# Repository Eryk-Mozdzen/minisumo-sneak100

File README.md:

# Autonomous minisumo robot Sneak100 

### DEADLINE:
```diff
#  4 sep 2021 - Baltic Robot Battles, Gdansk, Poland (canceled)
- 20 nov 2021 - EastROBO 2021, Bialystok, Poland (missed)
- 28 nov 2021 - ROBOmotion 2021, Rzeszow, Poland (missed)
+  9 apr 2022 - Robotic Tournament, Rybnik, Poland
# 13 may 2022 - Baltic Robot Battles, Gdansk, Poland (canceled)
+ 18 jun 2022 - XIII Robotic Arena, Wroclaw, Poland
-  2 jul 2022 - Drones And Robots Tournament, Krakow, Poland (missed)
+  4 nov 2022 - Robochallnge 2022, Bucharest, Romania
+ 26 nov 2022 - ROBOmotion 2022, Rzeszow, Poland
+  1 apr 2023 - Robotic Tournament, Rybnik, Poland
- 22 apr 2023 - XIV Robotic Arena, Wroclaw, Poland (malfunction)
- 14 may 2023 - Tournoi National de Robotique, Niem, France (malfunction)
```

### Next version:     
- develop spring for blade
- proximity sensors: turn to more front
- hide power switch

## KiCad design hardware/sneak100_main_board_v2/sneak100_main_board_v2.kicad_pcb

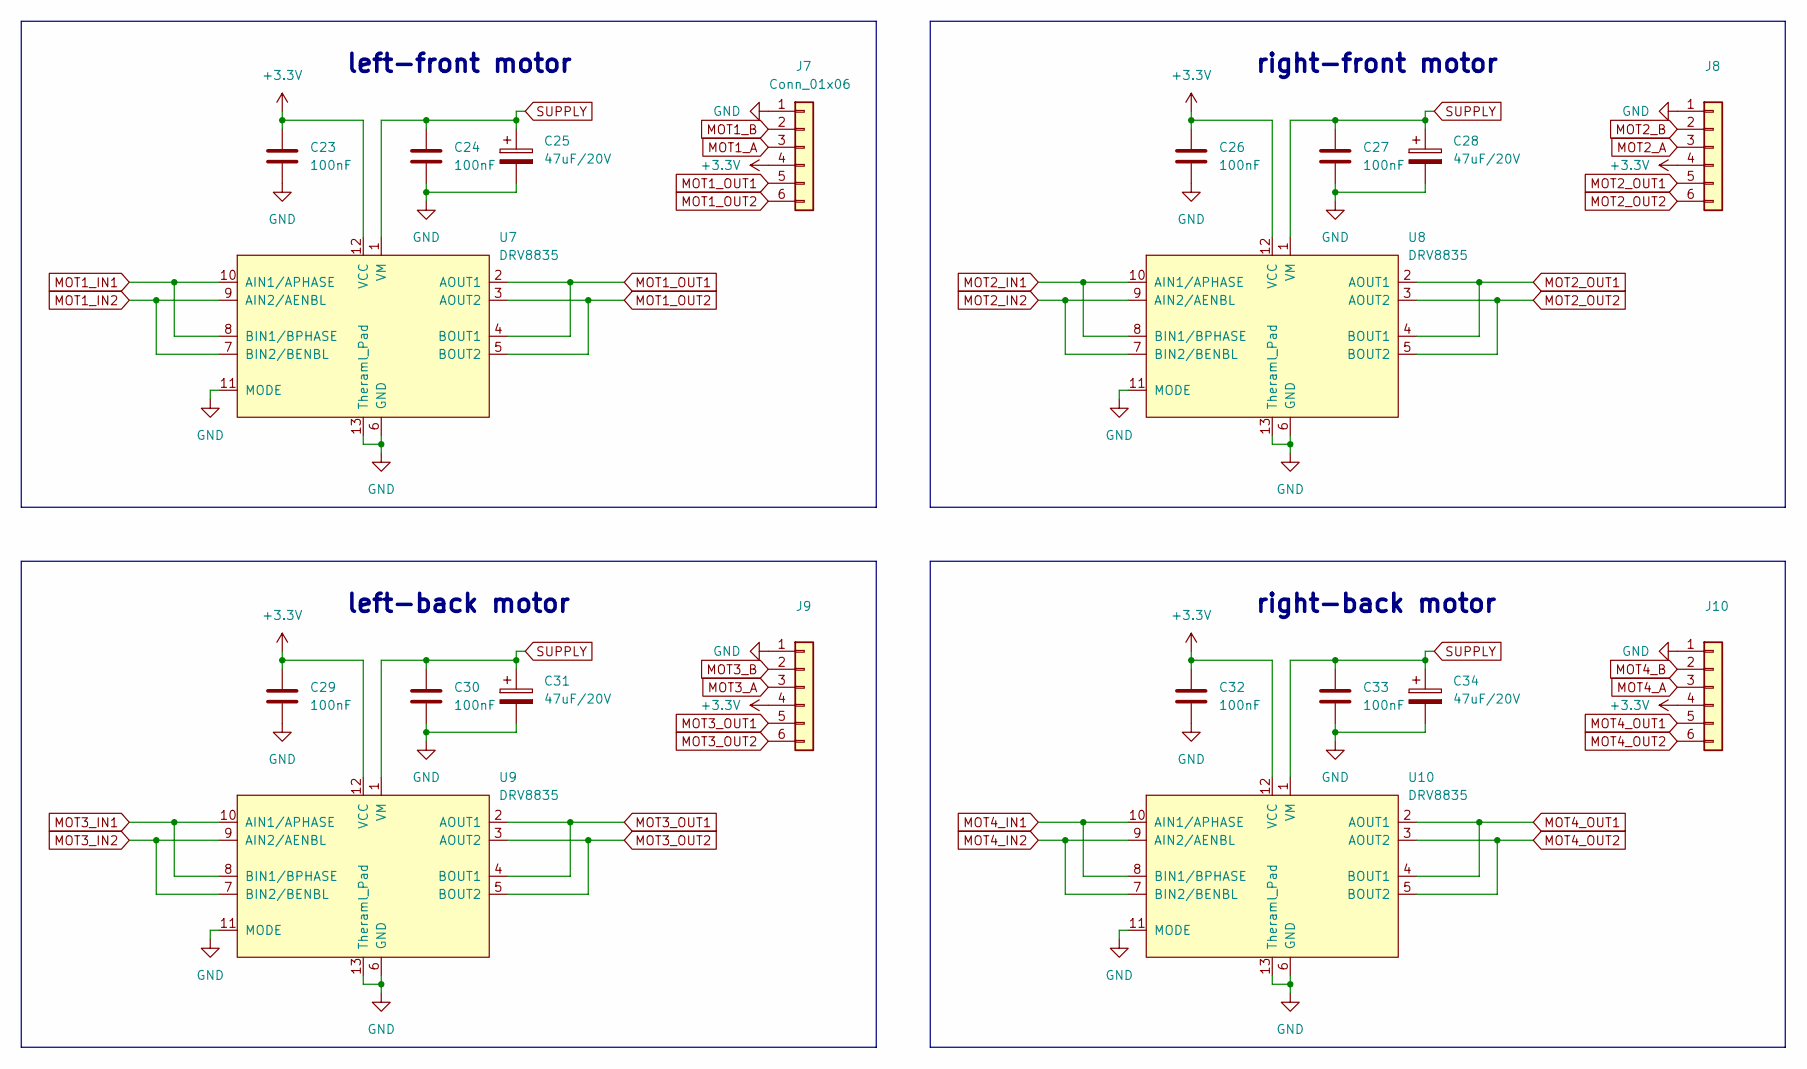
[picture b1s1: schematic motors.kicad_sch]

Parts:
C23, C24, C26, C27, C29, C30, C32, C33: 100nF
C25, C28, C31, C34: 47uF/20V
J7: Conn_01x06
J8, J9, J10: (no value)
U7, U8, U9, U10: DRV8835

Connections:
GND: C23.2, C24.2, C25.2, C26.2, C27.2, C28.2, C29.2, C30.2, C31.2, C32.2, C33.2, C34.2, J7.1, J8.1, J9.1, J10.1, U7.6 (GND), U7.11 (MODE), U7.13 (Theraml_Pad), U8.6 (GND), U8.11 (MODE), U8.13 (Theraml_Pad), U9.6 (GND), U9.11 (MODE), U9.13 (Theraml_Pad), U10.6 (GND), U10.11 (MODE), U10.13 (Theraml_Pad); also elsewhere on the board
MOT1_A: J7.3; also elsewhere on the board
MOT1_B: J7.2; also elsewhere on the board
MOT1_IN1: U7.8 (BIN1/BPHASE), U7.10 (AIN1/APHASE); also elsewhere on the board
MOT1_IN2: U7.7 (BIN2/BENBL), U7.9 (AIN2/AENBL); also elsewhere on the board
MOT1_OUT1: J7.5, U7.2 (AOUT1), U7.4 (BOUT1)
MOT1_OUT2: J7.6, U7.3 (AOUT2), U7.5 (BOUT2)
MOT2_A: J8.3; also elsewhere on the board
MOT2_B: J8.2; also elsewhere on the board
MOT2_IN1: U8.8 (BIN1/BPHASE), U8.10 (AIN1/APHASE); also elsewhere on the board
MOT2_IN2: U8.7 (BIN2/BENBL), U8.9 (AIN2/AENBL); also elsewhere on the board
MOT2_OUT1: J8.5, U8.2 (AOUT1), U8.4 (BOUT1)
MOT2_OUT2: J8.6, U8.3 (AOUT2), U8.5 (BOUT2)
MOT3_A: J9.3; also elsewhere on the board
MOT3_B: J9.2; also elsewhere on the board
MOT3_IN1: U9.8 (BIN1/BPHASE), U9.10 (AIN1/APHASE); also elsewhere on the board
MOT3_IN2: U9.7 (BIN2/BENBL), U9.9 (AIN2/AENBL); also elsewhere on the board
MOT3_OUT1: J9.5, U9.2 (AOUT1), U9.4 (BOUT1)
MOT3_OUT2: J9.6, U9.3 (AOUT2), U9.5 (BOUT2)
MOT4_A: J10.3; also elsewhere on the board
MOT4_B: J10.2; also elsewhere on the board
MOT4_IN1: U10.8 (BIN1/BPHASE), U10.10 (AIN1/APHASE); also elsewhere on the board
MOT4_IN2: U10.7 (BIN2/BENBL), U10.9 (AIN2/AENBL); also elsewhere on the board
MOT4_OUT1: J10.5, U10.2 (AOUT1), U10.4 (BOUT1)
MOT4_OUT2: J10.6, U10.3 (AOUT2), U10.5 (BOUT2)
SUPPLY: C24.1, C25.1, C27.1, C28.1, C30.1, C31.1, C33.1, C34.1, U7.1 (VM), U8.1 (VM), U9.1 (VM), U10.1 (VM); also elsewhere on the board

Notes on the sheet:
left-back motor
right-front motor
right-back motor
left-front motor

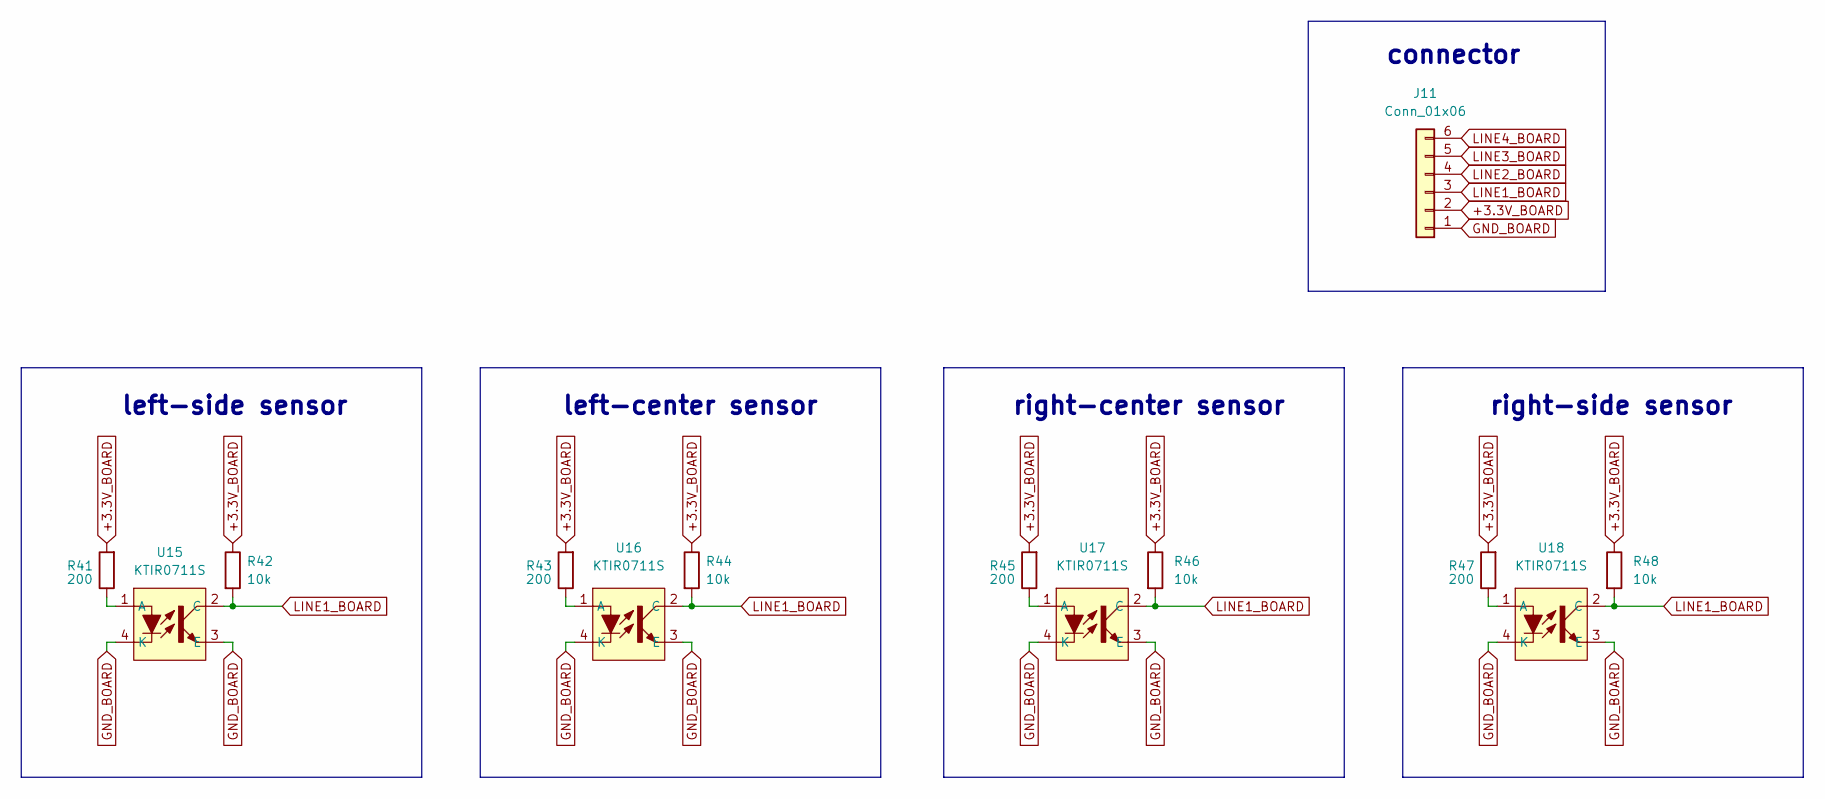
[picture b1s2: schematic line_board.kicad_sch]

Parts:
J11: Conn_01x06
R41, R43, R45, R47: 200
R42, R44, R46, R48: 10k
U15, U16, U17, U18: KTIR0711S

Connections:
+3.3V_BOARD: J11.2, R41.2, R42.1, R43.2, R44.1, R45.2, R46.1, R47.2, R48.1
GND_BOARD: J11.1, U15.3 (E), U15.4 (K), U16.3 (E), U16.4 (K), U17.3 (E), U17.4 (K), U18.3 (E), U18.4 (K)
LINE1_BOARD: J11.3, R42.2, R44.2, R46.2, R48.2, U15.2 (C), U16.2 (C), U17.2 (C), U18.2 (C)
LINE2_BOARD: J11.4
LINE3_BOARD: J11.5
LINE4_BOARD: J11.6
unnamed: R41.1, U15.1 (A)
unnamed: R43.1, U16.1 (A)
unnamed: R45.1, U17.1 (A)
unnamed: R47.1, U18.1 (A)

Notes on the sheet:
left-side sensor
right-center sensor
connector
right-side sensor
left-center sensor

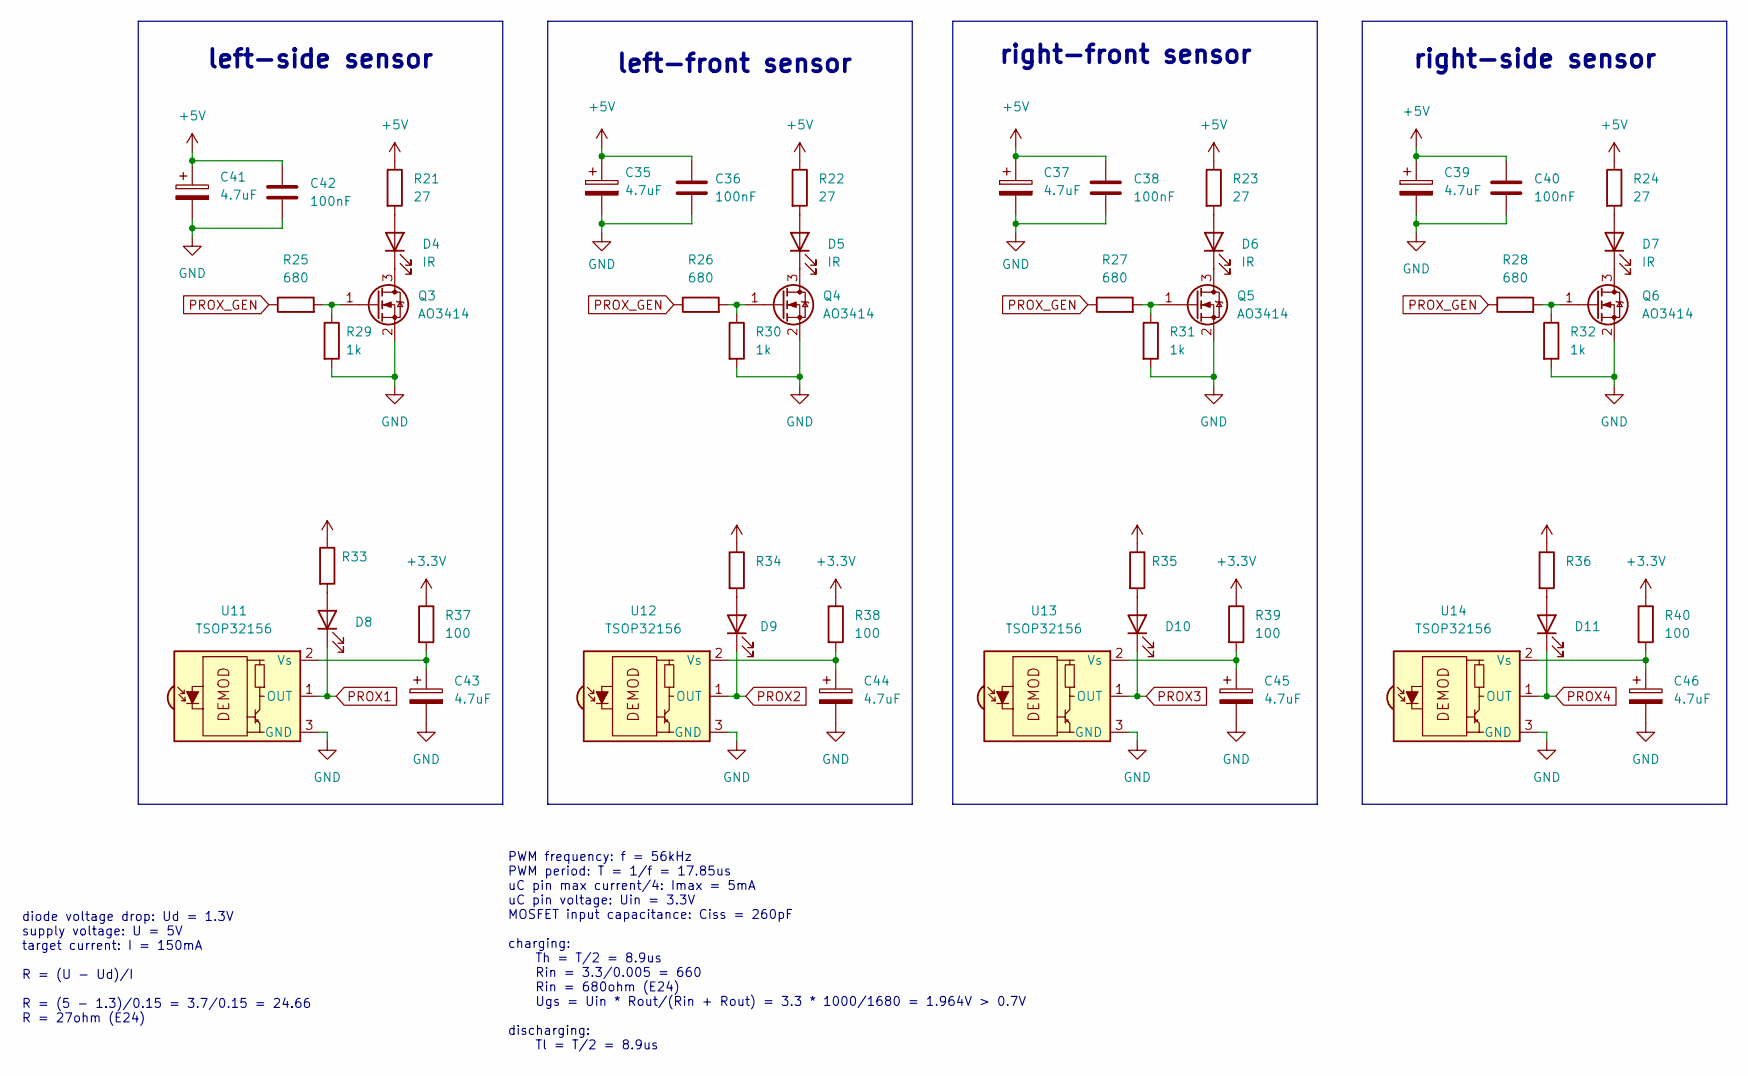
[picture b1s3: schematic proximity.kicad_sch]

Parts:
C35, C37, C39, C41, C43, C44, C45, C46: 4.7uF
C36, C38, C40, C42: 100nF
D4, D5, D6, D7: IR
D8, D9, D10, D11: (no value)
Q3, Q4, Q5, Q6: AO3414; SOT-23
R21, R22, R23, R24: 27
R25, R26, R27, R28: 680
R29, R30, R31, R32: 1k
R33, R34, R35, R36: (no value)
R37, R38, R39, R40: 100
U11, U12, U13, U14: TSOP32156; Vishay_MOLD-3Pin

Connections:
+5V: C35.1, C36.1, C37.1, C38.1, C39.1, C40.1, C41.1, C42.1, R21.1, R22.1, R23.1, R24.1; also elsewhere on the board
GND: C35.2, C36.2, C37.2, C38.2, C39.2, C40.2, C41.2, C42.2, C43.2, C44.2, C45.2, C46.2, Q3.2 (S), Q4.2 (S), Q5.2 (S), Q6.2 (S), R29.2, R30.2, R31.2, R32.2, U11.3 (GND), U12.3 (GND), U13.3 (GND), U14.3 (GND); also elsewhere on the board
unnamed: C43.1, R37.2, U11.2 (Vs)
unnamed: C44.1, R38.2, U12.2 (Vs)
unnamed: C45.1, R39.2, U13.2 (Vs)
unnamed: C46.1, R40.2, U14.2 (Vs)
unnamed: D4.1 (K), Q3.3 (D)
unnamed: D4.2 (A), R21.2
unnamed: D5.1 (K), Q4.3 (D)
unnamed: D5.2 (A), R22.2
unnamed: D6.1 (K), Q5.3 (D)
unnamed: D6.2 (A), R23.2
unnamed: D7.1 (K), Q6.3 (D)
unnamed: D7.2 (A), R24.2
unnamed: D8.2 (A), R33.2
unnamed: D9.2 (A), R34.2
unnamed: D10.2 (A), R35.2
unnamed: D11.2 (A), R36.2
unnamed: Q3.1 (G), R25.2, R29.1
unnamed: Q4.1 (G), R26.2, R30.1
unnamed: Q5.1 (G), R27.2, R31.1
unnamed: Q6.1 (G), R28.2, R32.1
PROX1: D8.1 (K), U11.1 (OUT); also elsewhere on the board
PROX2: D9.1 (K), U12.1 (OUT); also elsewhere on the board
PROX3: D10.1 (K), U13.1 (OUT); also elsewhere on the board
PROX4: D11.1 (K), U14.1 (OUT); also elsewhere on the board
PROX_GEN: R25.1, R26.1, R27.1, R28.1; also elsewhere on the board

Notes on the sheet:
left-side sensor
left-front sensor
right-side sensor
PWM frequency: f = 56kHz PWM period: T = 1/f = 17.85us uC pin max current/4: Imax = 5mA uC pin voltage: Uin = 3.3V MOSFET input capacitance: Ciss = 260pF charging: Th = T/2 = 8.9us Rin = 3.3/0.005 = 660 Rin = 680ohm (E24) Ugs = Uin * Rout/(Rin + Rout) = 3.3 * 1000/1680 = 1.964V > 0.7V discharging: 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
right-front sensor
diode voltage drop: Ud = 1.3V supply voltage: U = 5V target current: I = 150mA R = (U - Ud)/I R = (5 - 1.3)/0.15 = 3.7/0.15 = 24.66 R = 27ohm (E24)

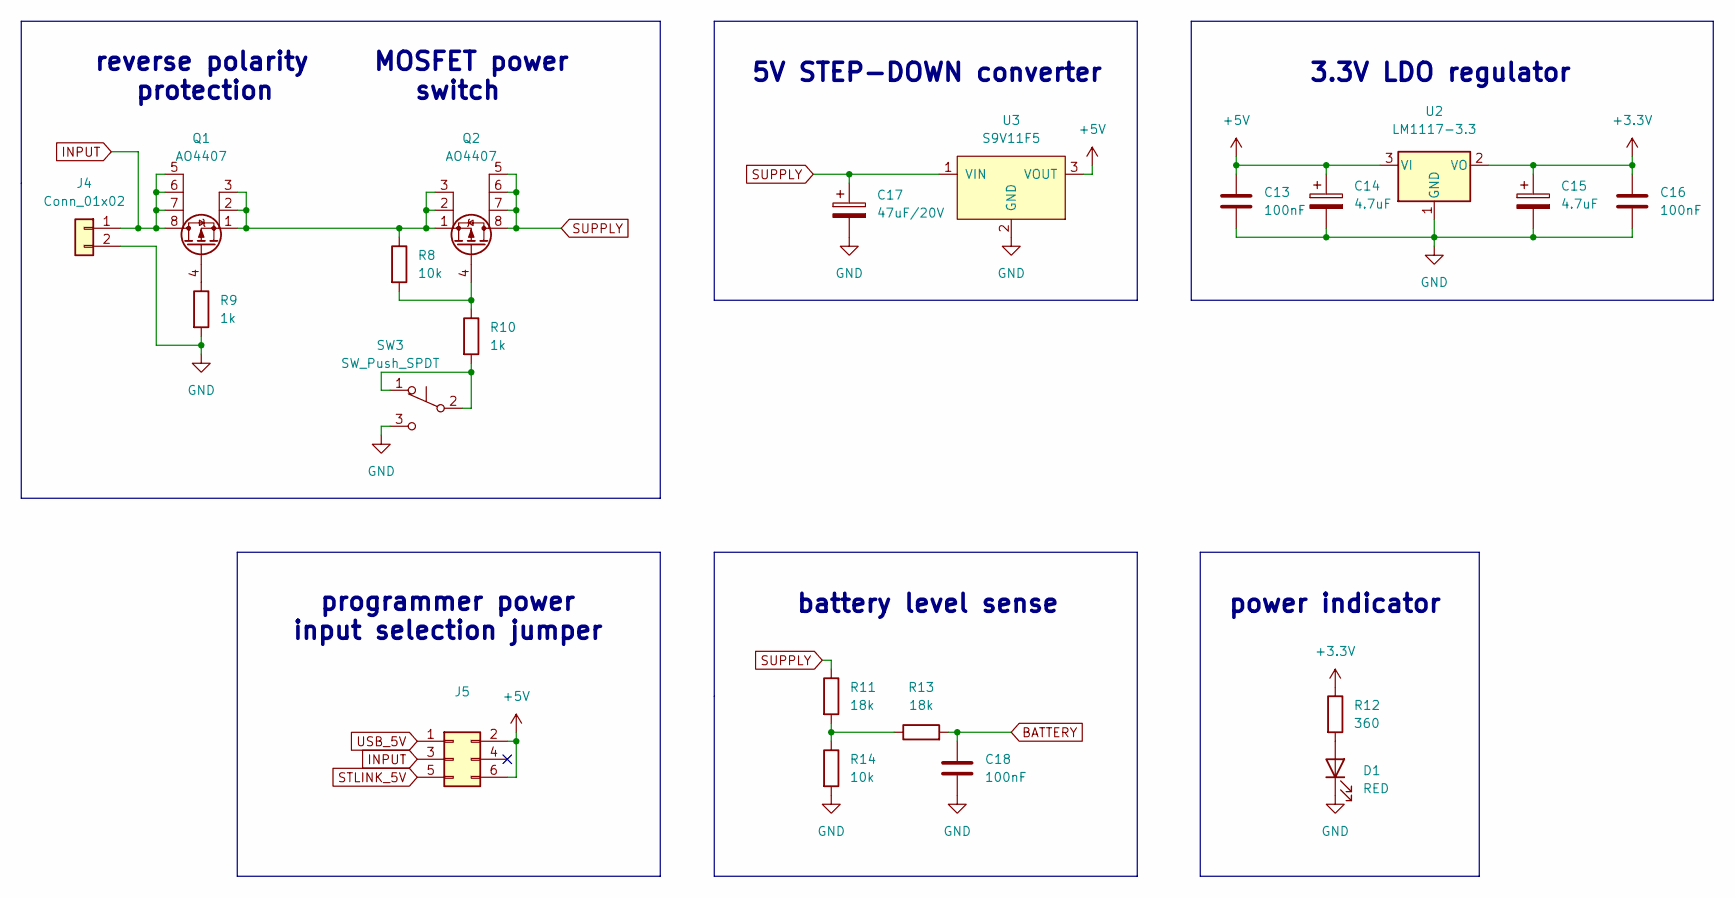
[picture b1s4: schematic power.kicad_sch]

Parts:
C13, C16, C18: 100nF
C14, C15: 4.7uF
C17: 47uF/20V
D1: RED
J4: Conn_01x02
J5: (no value)
Q1, Q2: AO4407
R8, R14: 10k
R9, R10: 1k
R11, R13: 18k
R12: 360
SW3: SW_Push_SPDT
U2: LM1117-3.3
U3: S9V11F5

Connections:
+5V: C13.1, C14.1, J5.2, J5.6, U2.3 (VI), U3.3 (VOUT); also elsewhere on the board
BATTERY: C18.1, R13.2; also elsewhere on the board
GND: C13.2, C14.2, C15.2, C16.2, C17.2, C18.2, D1.1 (K), J4.2, R9.2, R14.2, SW3.3 (C), U2.1 (GND), U3.2 (GND); also elsewhere on the board
INPUT: J4.1, J5.3, Q1.5, Q1.6, Q1.7, Q1.8
unnamed: D1.2 (A), R12.2
unnamed: Q1.1, Q1.2, Q1.3, Q2.1, Q2.2, Q2.3, R8.1
unnamed: Q1.4, R9.1
unnamed: Q2.4, R8.2, R10.1
unnamed: R10.2, SW3.1 (A), SW3.2 (B)
unnamed: R11.2, R13.1, R14.1
STLINK_5V: J5.5; also elsewhere on the board
SUPPLY: C17.1, Q2.5, Q2.6, Q2.7, Q2.8, R11.1, U3.1 (VIN); also elsewhere on the board
USB_5V: J5.1; also elsewhere on the board

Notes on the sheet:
battery level sense
MOSFET power switch
5V STEP-DOWN converter
programmer power input selection jumper
reverse polarity protection
power indicator
3.3V LDO regulator

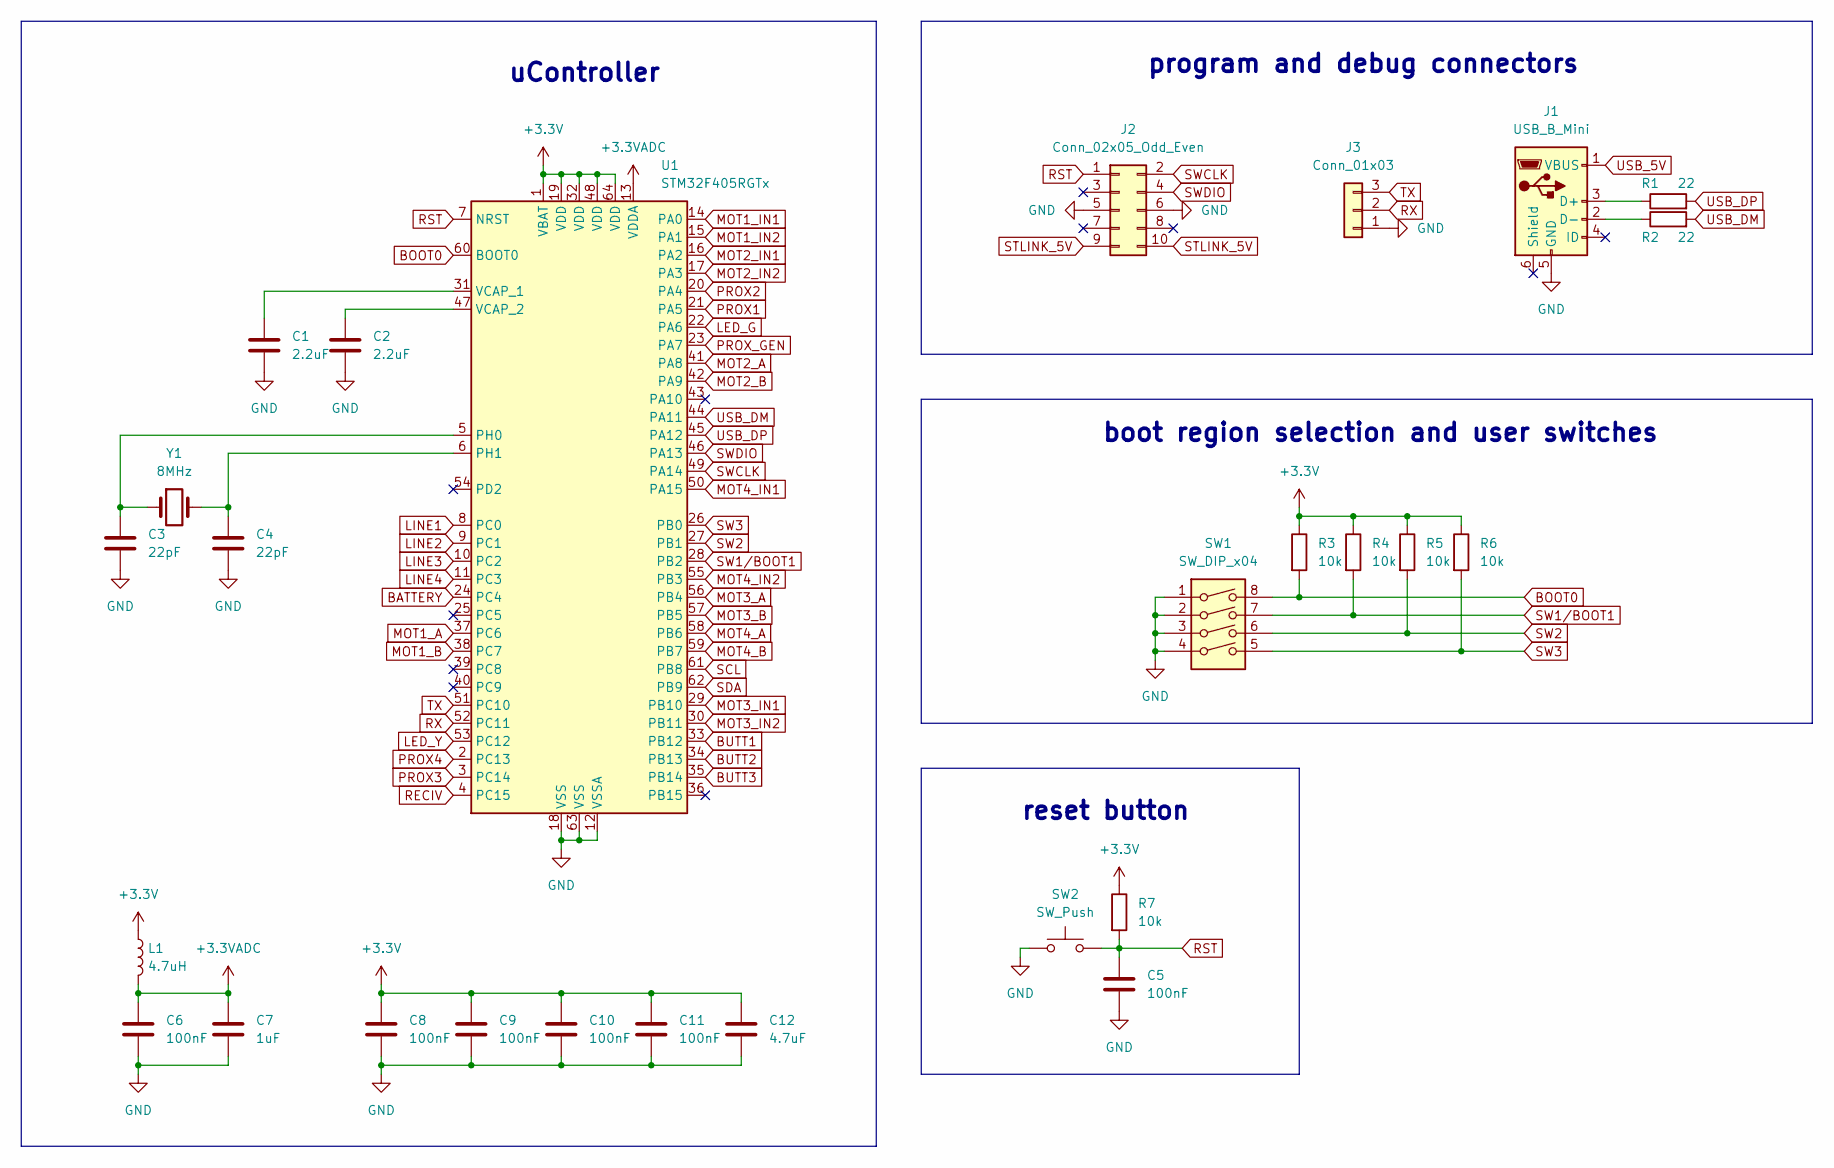
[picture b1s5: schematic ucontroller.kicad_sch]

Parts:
C1, C2: 2.2uF
C3, C4: 22pF
C5, C6, C8, C9, C10, C11: 100nF
C7: 1uF
C12: 4.7uF
J1: USB_B_Mini
J2: Conn_02x05_Odd_Even
J3: Conn_01x03
L1: 4.7uH
R1, R2: 22
R3, R4, R5, R6, R7: 10k
SW1: SW_DIP_x04
SW2: SW_Push
U1: STM32F405RGTx; LQFP-64_10x10mm_P0.5mm
Y1: 8MHz

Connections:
+3.3VADC: C6.1, C7.1, L1.2, U1.13 (VDDA)
BATTERY: U1.24 (PC4); also elsewhere on the board
BOOT0: R3.2, SW1.8, U1.60 (BOOT0)
BUTT1: U1.33 (PB12); also elsewhere on the board
BUTT2: U1.34 (PB13); also elsewhere on the board
BUTT3: U1.35 (PB14); also elsewhere on the board
GND: C1.2, C2.2, C3.2, C4.2, C5.2, C6.2, C7.2, C8.2, C9.2, C10.2, C11.2, C12.2, J1.5 (GND), J2.5, J2.6, J3.1, SW1.1, SW1.2, SW1.3, SW1.4, SW2.1, U1.12 (VSSA), U1.18 (VSS), U1.63 (VSS); also elsewhere on the board
LED_G: U1.22 (PA6); also elsewhere on the board
LED_Y: U1.53 (PC12); also elsewhere on the board
LINE1: U1.8 (PC0); also elsewhere on the board
LINE2: U1.9 (PC1); also elsewhere on the board
LINE3: U1.10 (PC2); also elsewhere on the board
LINE4: U1.11 (PC3); also elsewhere on the board
MOT1_A: U1.37 (PC6); also elsewhere on the board
MOT1_B: U1.38 (PC7); also elsewhere on the board
MOT1_IN1: U1.14 (PA0); also elsewhere on the board
MOT1_IN2: U1.15 (PA1); also elsewhere on the board
MOT2_A: U1.41 (PA8); also elsewhere on the board
MOT2_B: U1.42 (PA9); also elsewhere on the board
MOT2_IN1: U1.16 (PA2); also elsewhere on the board
MOT2_IN2: U1.17 (PA3); also elsewhere on the board
MOT3_A: U1.56 (PB4); also elsewhere on the board
MOT3_B: U1.57 (PB5); also elsewhere on the board
MOT3_IN1: U1.29 (PB10); also elsewhere on the board
MOT3_IN2: U1.30 (PB11); also elsewhere on the board
MOT4_A: U1.58 (PB6); also elsewhere on the board
MOT4_B: U1.59 (PB7); also elsewhere on the board
MOT4_IN1: U1.50 (PA15); also elsewhere on the board
MOT4_IN2: U1.55 (PB3); also elsewhere on the board
unnamed: C1.1, U1.31 (VCAP_1)
unnamed: C2.1, U1.47 (VCAP_2)
unnamed: C3.1, U1.5 (PH0), Y1.1
unnamed: C4.1, U1.6 (PH1), Y1.2
unnamed: J1.2 (D-), R2.1
unnamed: J1.3 (D+), R1.1
PROX1: U1.21 (PA5); also elsewhere on the board
PROX2: U1.20 (PA4); also elsewhere on the board
PROX3: U1.3 (PC14); also elsewhere on the board
PROX4: U1.2 (PC13); also elsewhere on the board
PROX_GEN: U1.23 (PA7); also elsewhere on the board
RECIV: U1.4 (PC15); also elsewhere on the board
RST: C5.1, J2.1, R7.2, SW2.2, U1.7 (NRST)
RX: J3.2, U1.52 (PC11)
SCL: U1.61 (PB8); also elsewhere on the board
SDA: U1.62 (PB9); also elsewhere on the board
STLINK_5V: J2.9, J2.10; also elsewhere on the board
SW1/BOOT1: R4.2, SW1.7, U1.28 (PB2)
SW2: R5.2, SW1.6, U1.27 (PB1)
SW3: R6.2, SW1.5, U1.26 (PB0)
SWCLK: J2.2, U1.49 (PA14)
SWDIO: J2.4, U1.46 (PA13)
TX: J3.3, U1.51 (PC10)
USB_5V: J1.1 (VBUS); also elsewhere on the board
USB_DM: R2.2, U1.44 (PA11)
USB_DP: R1.2, U1.45 (PA12)

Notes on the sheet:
uController
reset button
program and debug connectors
boot region selection and user switches

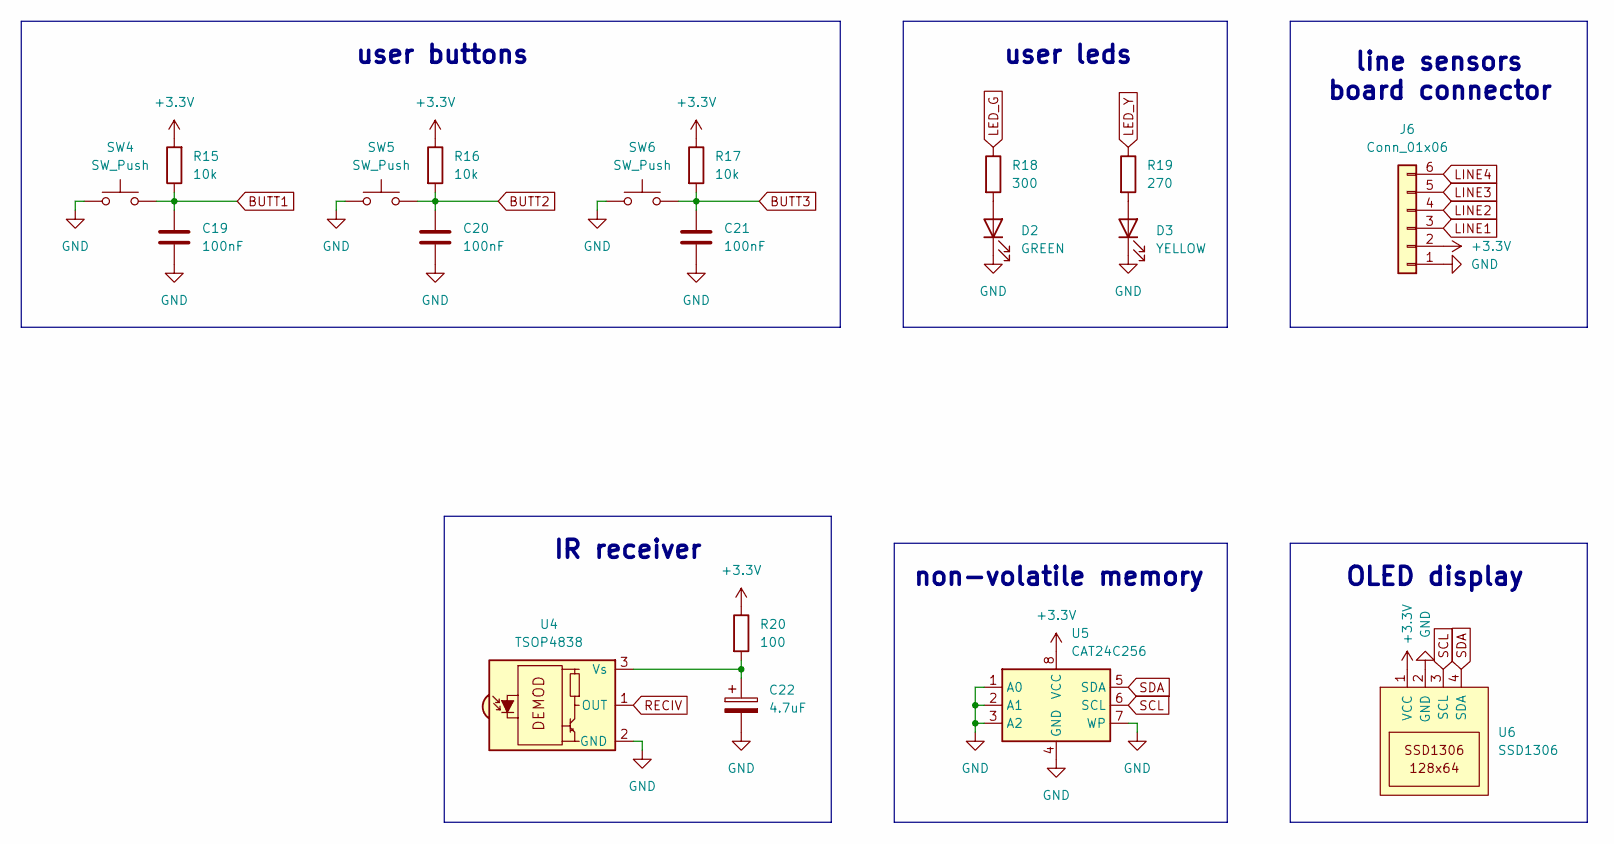
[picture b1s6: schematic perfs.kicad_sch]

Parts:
C19, C20, C21: 100nF
C22: 4.7uF
D2: GREEN
D3: YELLOW
J6: Conn_01x06
R15, R16, R17: 10k
R18: 300
R19: 270
R20: 100
SW4, SW5, SW6: SW_Push
U4: TSOP4838
U5: CAT24C256
U6: SSD1306

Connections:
BUTT1: C19.1, R15.1, SW4.2; also elsewhere on the board
BUTT2: C20.1, R16.2, SW5.2; also elsewhere on the board
BUTT3: C21.1, R17.2, SW6.2; also elsewhere on the board
GND: C19.2, C20.2, C21.2, C22.2, D2.1 (K), D3.1 (K), J6.1, SW4.1, SW5.1, SW6.1, U4.2 (GND), U5.1 (A0), U5.2 (A1), U5.3 (A2), U5.4 (GND), U5.7 (WP), U6.2 (GND); also elsewhere on the board
LED_G: R18.1; also elsewhere on the board
LED_Y: R19.1; also elsewhere on the board
LINE1: J6.3; also elsewhere on the board
LINE2: J6.4; also elsewhere on the board
LINE3: J6.5; also elsewhere on the board
LINE4: J6.6; also elsewhere on the board
unnamed: C22.1, R20.2, U4.3 (Vs)
unnamed: D2.2 (A), R18.2
unnamed: D3.2 (A), R19.2
RECIV: U4.1 (OUT); also elsewhere on the board
SCL: U5.6 (SCL), U6.3 (SCL); also elsewhere on the board
SDA: U5.5 (SDA), U6.4 (SDA); also elsewhere on the board

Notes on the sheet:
OLED display
non-volatile memory
IR receiver
user buttons
user leds
line sensors board connector

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
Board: 2 copper layers, 144 parts (11 on the bottom side), 98 nets, no tracks yet.

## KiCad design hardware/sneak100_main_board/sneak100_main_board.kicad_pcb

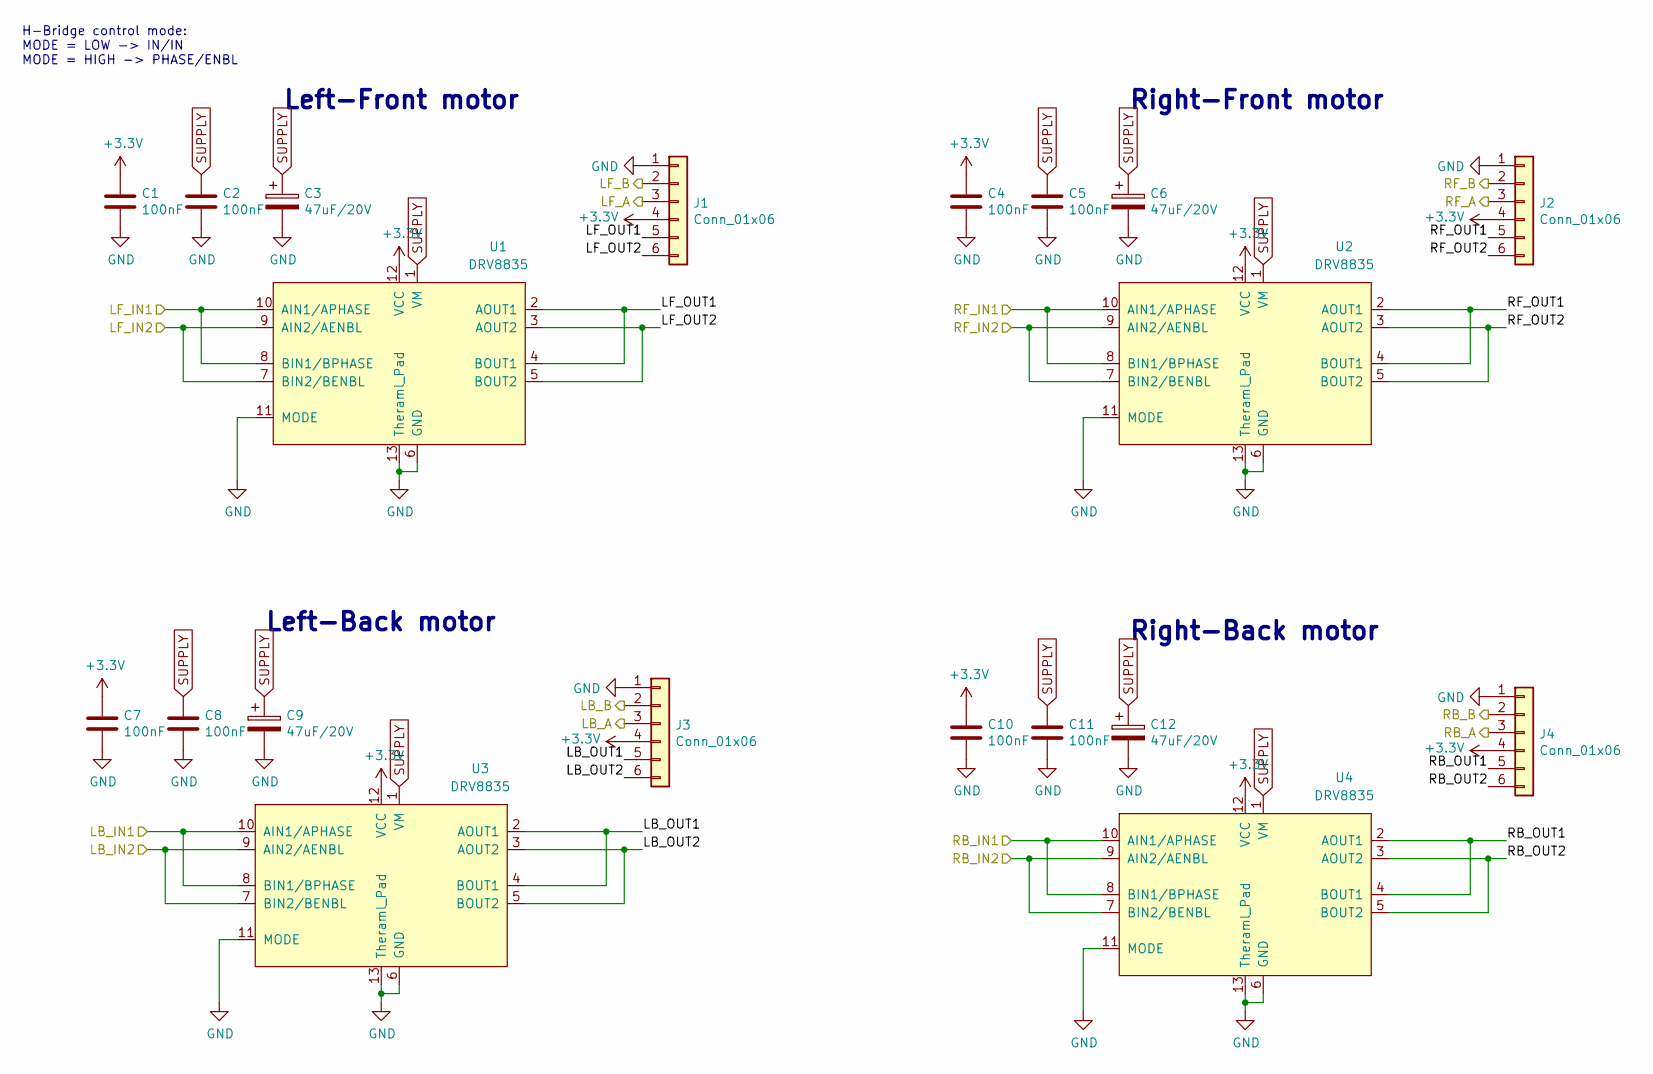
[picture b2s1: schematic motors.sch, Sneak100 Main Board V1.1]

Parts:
C1, C2, C4, C5, C7, C8, C10, C11: 100nF; C_0603_1608Metric
C3, C6, C9, C12: 47uF/20V; CP_EIA-7343-31_Kemet-D
J1, J2, J3, J4: Conn_01x06; PinSocket_1x06_P2.54mm_Horizontal
U1, U2, U3, U4: DRV8835; DRV8835_hand_solder

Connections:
+3V3: C1.1, C4.1, C7.1, C10.1, J1.4, J2.4, J3.4, J4.4, U1.12 (VCC), U2.12 (VCC), U3.12 (VCC), U4.12 (VCC); also elsewhere on the board
/controller/LB_A: J3.3; also elsewhere on the board
/controller/LB_B: J3.2; also elsewhere on the board
/controller/LB_IN1: U3.8 (BIN1/BPHASE), U3.10 (AIN1/APHASE); also elsewhere on the board
/controller/LB_IN2: U3.7 (BIN2/BENBL), U3.9 (AIN2/AENBL); also elsewhere on the board
/controller/LF_A: J1.3; also elsewhere on the board
/controller/LF_B: J1.2; also elsewhere on the board
/controller/LF_IN1: U1.8 (BIN1/BPHASE), U1.10 (AIN1/APHASE); also elsewhere on the board
/controller/LF_IN2: U1.7 (BIN2/BENBL), U1.9 (AIN2/AENBL); also elsewhere on the board
/controller/RB_A: J4.3; also elsewhere on the board
/controller/RB_B: J4.2; also elsewhere on the board
/controller/RB_IN1: U4.8 (BIN1/BPHASE), U4.10 (AIN1/APHASE); also elsewhere on the board
/controller/RB_IN2: U4.7 (BIN2/BENBL), U4.9 (AIN2/AENBL); also elsewhere on the board
/controller/RF_A: J2.3; also elsewhere on the board
/controller/RF_B: J2.2; also elsewhere on the board
/controller/RF_IN1: U2.8 (BIN1/BPHASE), U2.10 (AIN1/APHASE); also elsewhere on the board
/controller/RF_IN2: U2.7 (BIN2/BENBL), U2.9 (AIN2/AENBL); also elsewhere on the board
/motors/LB_OUT1: J3.5, U3.2 (AOUT1), U3.4 (BOUT1)
/motors/LB_OUT2: J3.6, U3.3 (AOUT2), U3.5 (BOUT2)
/motors/LF_OUT1: J1.5, U1.2 (AOUT1), U1.4 (BOUT1)
/motors/LF_OUT2: J1.6, U1.3 (AOUT2), U1.5 (BOUT2)
/motors/RB_OUT1: J4.5, U4.2 (AOUT1), U4.4 (BOUT1)
/motors/RB_OUT2: J4.6, U4.3 (AOUT2), U4.5 (BOUT2)
/motors/RF_OUT1: J2.5, U2.2 (AOUT1), U2.4 (BOUT1)
/motors/RF_OUT2: J2.6, U2.3 (AOUT2), U2.5 (BOUT2)
GND: C1.2, C2.2, C3.2, C4.2, C5.2, C6.2, C7.2, C8.2, C9.2, C10.2, C11.2, C12.2, J1.1, J2.1, J3.1, J4.1, U1.6 (GND), U1.11 (MODE), U1.13 (Theraml_Pad), U2.6 (GND), U2.11 (MODE), U2.13 (Theraml_Pad), U3.6 (GND), U3.11 (MODE), U3.13 (Theraml_Pad), U4.6 (GND), U4.11 (MODE), U4.13 (Theraml_Pad); also elsewhere on the board
SUPPLY: C2.1, C3.1, C5.1, C6.1, C8.1, C9.1, C11.1, C12.1, U1.1 (VM), U2.1 (VM), U3.1 (VM), U4.1 (VM); also elsewhere on the board

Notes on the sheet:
H-Bridge control mode: MODE = LOW -> IN/IN MODE = HIGH -> PHASE/ENBL
Left-Front motor
Right-Front motor
Left-Back motor
Right-Back motor

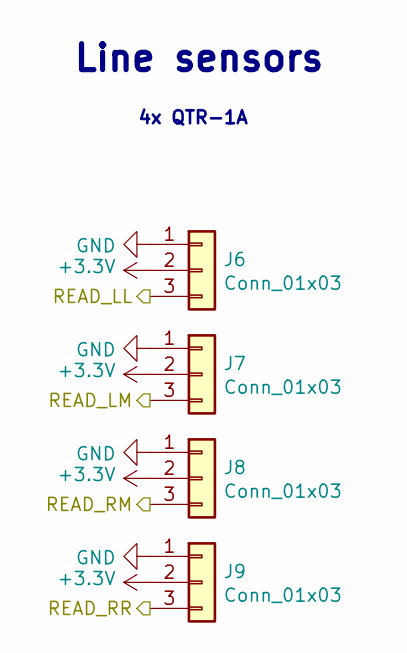
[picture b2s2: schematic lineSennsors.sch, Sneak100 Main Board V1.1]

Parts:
J6, J7, J8, J9: Conn_01x03; PinSocket_1x03_P2.54mm_Vertical

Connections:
+3V3: J6.2, J7.2, J8.2, J9.2; also elsewhere on the board
/controller/LINE_LL: J6.3; also elsewhere on the board
/controller/LINE_LM: J7.3; also elsewhere on the board
/controller/LINE_RM: J8.3; also elsewhere on the board
/controller/LINE_RR: J9.3; also elsewhere on the board
GND: J6.1, J7.1, J8.1, J9.1; also elsewhere on the board

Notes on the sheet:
Line sensors
4x QTR-1A
